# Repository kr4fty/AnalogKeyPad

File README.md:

Fork of the library made by oryshed (oryshed dot gmail dot com)

**Original**: [http://www.oryshed.com/arduino/lcd-48x84-shield] (http://www.oryshed.com/arduino/lcd-48x84-shield)

Library that gives us the possibility to use up to 5 buttons connected to a single analog port.

## Hardware

<p align="center">
  <br><br>
  <b>Circuito</b><br>
  
  <br><br>
  <b>Vista 3D</b><br>
  
</p>

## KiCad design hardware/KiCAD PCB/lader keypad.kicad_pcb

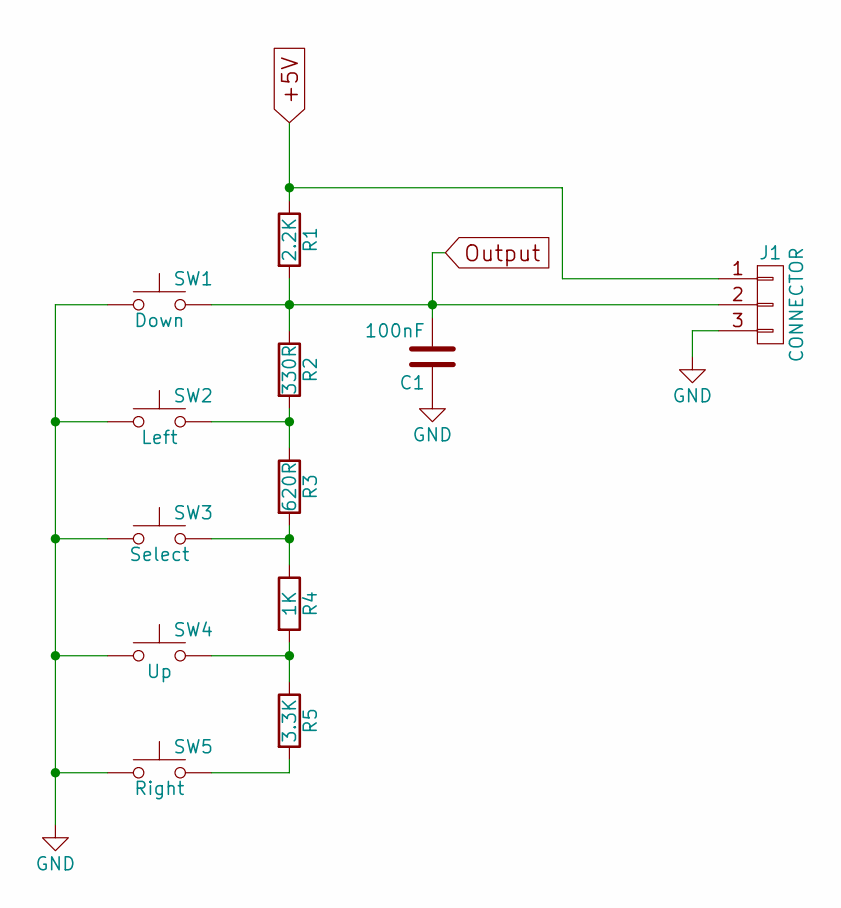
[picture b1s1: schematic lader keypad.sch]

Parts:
C1: 100nF; C_Disc_D6.0mm_W2.5mm_P5.00mm
J1: CONNECTOR; Pin_Header_Straight_1x03_Pitch2.54mm
R1: 2.2K; R_Axial_DIN0204_L3.6mm_D1.6mm_P7.62mm_Horizontal
R2: 330R; R_Axial_DIN0204_L3.6mm_D1.6mm_P7.62mm_Horizontal
R3: 620R; R_Axial_DIN0204_L3.6mm_D1.6mm_P7.62mm_Horizontal
R4: 1K; R_Axial_DIN0204_L3.6mm_D1.6mm_P7.62mm_Horizontal
R5: 3.3K; R_Axial_DIN0204_L3.6mm_D1.6mm_P7.62mm_Horizontal
SW1: Down; SW_PUSH_6mm
SW2: Left; SW_PUSH_6mm
SW3: Select; SW_PUSH_6mm
SW4: Up; SW_PUSH_6mm
SW5: Right; SW_PUSH_6mm

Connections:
+5V: J1.1, R1.1
GND: C1.1, J1.3, SW1.1, SW2.1, SW3.1, SW4.1, SW5.1
unnamed: R2.2, R3.1, SW2.2
unnamed: R3.2, R4.1, SW3.2
unnamed: R4.2, R5.1, SW4.2
unnamed: R5.2, SW5.2
Output: C1.2, J1.2, R1.2, R2.1, SW1.2

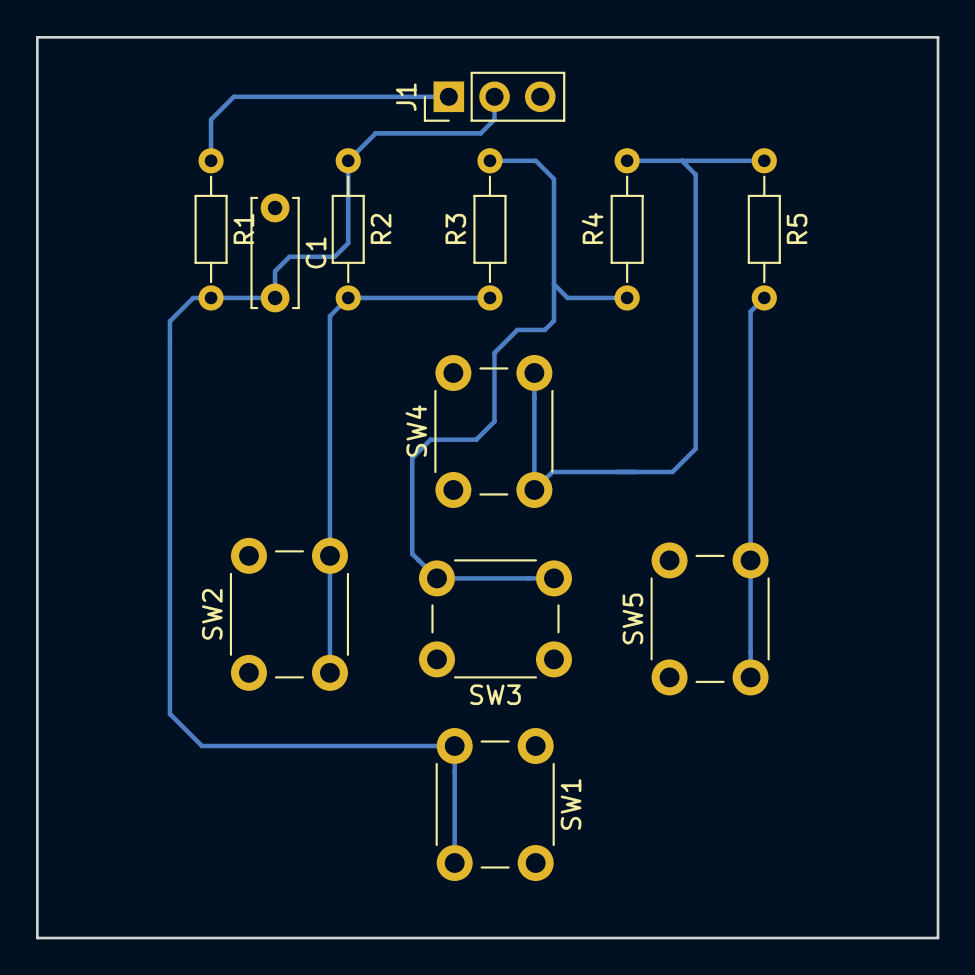
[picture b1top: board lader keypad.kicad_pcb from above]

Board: 2 copper layers, 50.0 x 50.0 mm, 12 parts (0 on the bottom side), 7 nets.

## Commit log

2017-03-02 hardware
2017-06-01 update schematic
2017-06-01 add .gitattributes
2017-07-10 update hardware
